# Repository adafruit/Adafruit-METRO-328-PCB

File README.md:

## Adafruit METRO 328 PCB

<a href="http://www.adafruit.com/products/2466"><br/>
Click here to purchase one from the Adafruit shop</a>

PCB files for the Adafruit METRO 328. Format is EagleCAD schematic and board layout

For more details, check out the product page at
* https://www.adafruit.com/products/2466

### Description

We sure love the ATmega328 here at Adafruit, and we use them a lot for our own projects. The processor has plenty of GPIO, Analog inputs, hardware UART SPI and I2C, timers and PWM galore - just enough for most simple projects. When we need to go small, we use a Metro Mini, but when size isn't as much of a concern, and a USB-serial converter is required, we reach for an Adafruit METRO.

METRO is the culmination of years of playing with AVRs: we wanted to make a development board that is easy to use and is hacker friendly.

ATmega328 brains - This popular chip has 32KB of flash (1/2 K is reserved for the bootloader), 2KB of RAM, clocked at 16MHz
Power the METRO with 7-9V polarity protected DC or the micro USB connector to any 5V USB source. The 2.1mm DC jack has an on/off switch next to it so you can turn off your setup easily. The METRO will automagically switch between USB and DC.
METRO has 20 GPIO pins, 6 of which are Analog in as well, and 2 of which are reserved for the USB-serial converter. There's also 6 PWMs available on 3 timers (1 x 16-bit, 2 x 8-bit). There's a hardware SPI port, hardware I2C port and hardware UART to USB.
GPIO Logic level is 5V but by cutting and soldering closed a jumper, you can easily convert it to 3.3V logic
USB to Serial converter, there's a hardware USB to Serial converter that can be used by any computer to listen/send data to the METRO, and can also be used to launch and update code via the bootloader
Four indicator LEDs, on the front edge of the PCB, for easy debugging. One green power LED, two RX/TX LEDs for the UART, and a red LED connected to pin PB5
Easy reprogramming, comes pre-loaded with the Optiboot bootloader, which is supported by avrdude and only uses 512 bytes.
Beautiful styling by PaintYourDragon and Bruce Yan, in Adafruit Black with gold plated pads.
Works with all Adafruit designed shields!
This version of the METRO 328 comes as a fully assembled and tested development board but without any headers or the DC jack attached. We do include these parts so that you can solder on if you like, or you can solder wires or header directly to the breakout pads. We also include 4 rubber bumpers to keep it from slipping off your desk.

### License

Adafruit invests time and resources providing this open source design, please support Adafruit and open-source hardware by purchasing products from [Adafruit](https://www.adafruit.com)!

Designed by Limor Fried/Ladyada for Adafruit Industries.

Creative Commons Attribution/Share-Alike. See license.txt for additional details.

Derivative of "Arduino UNO R3 Reference design" (http://www.arduino.cc/en/Main/ArduinoBoardUno)

All text above must be included in any redistribution

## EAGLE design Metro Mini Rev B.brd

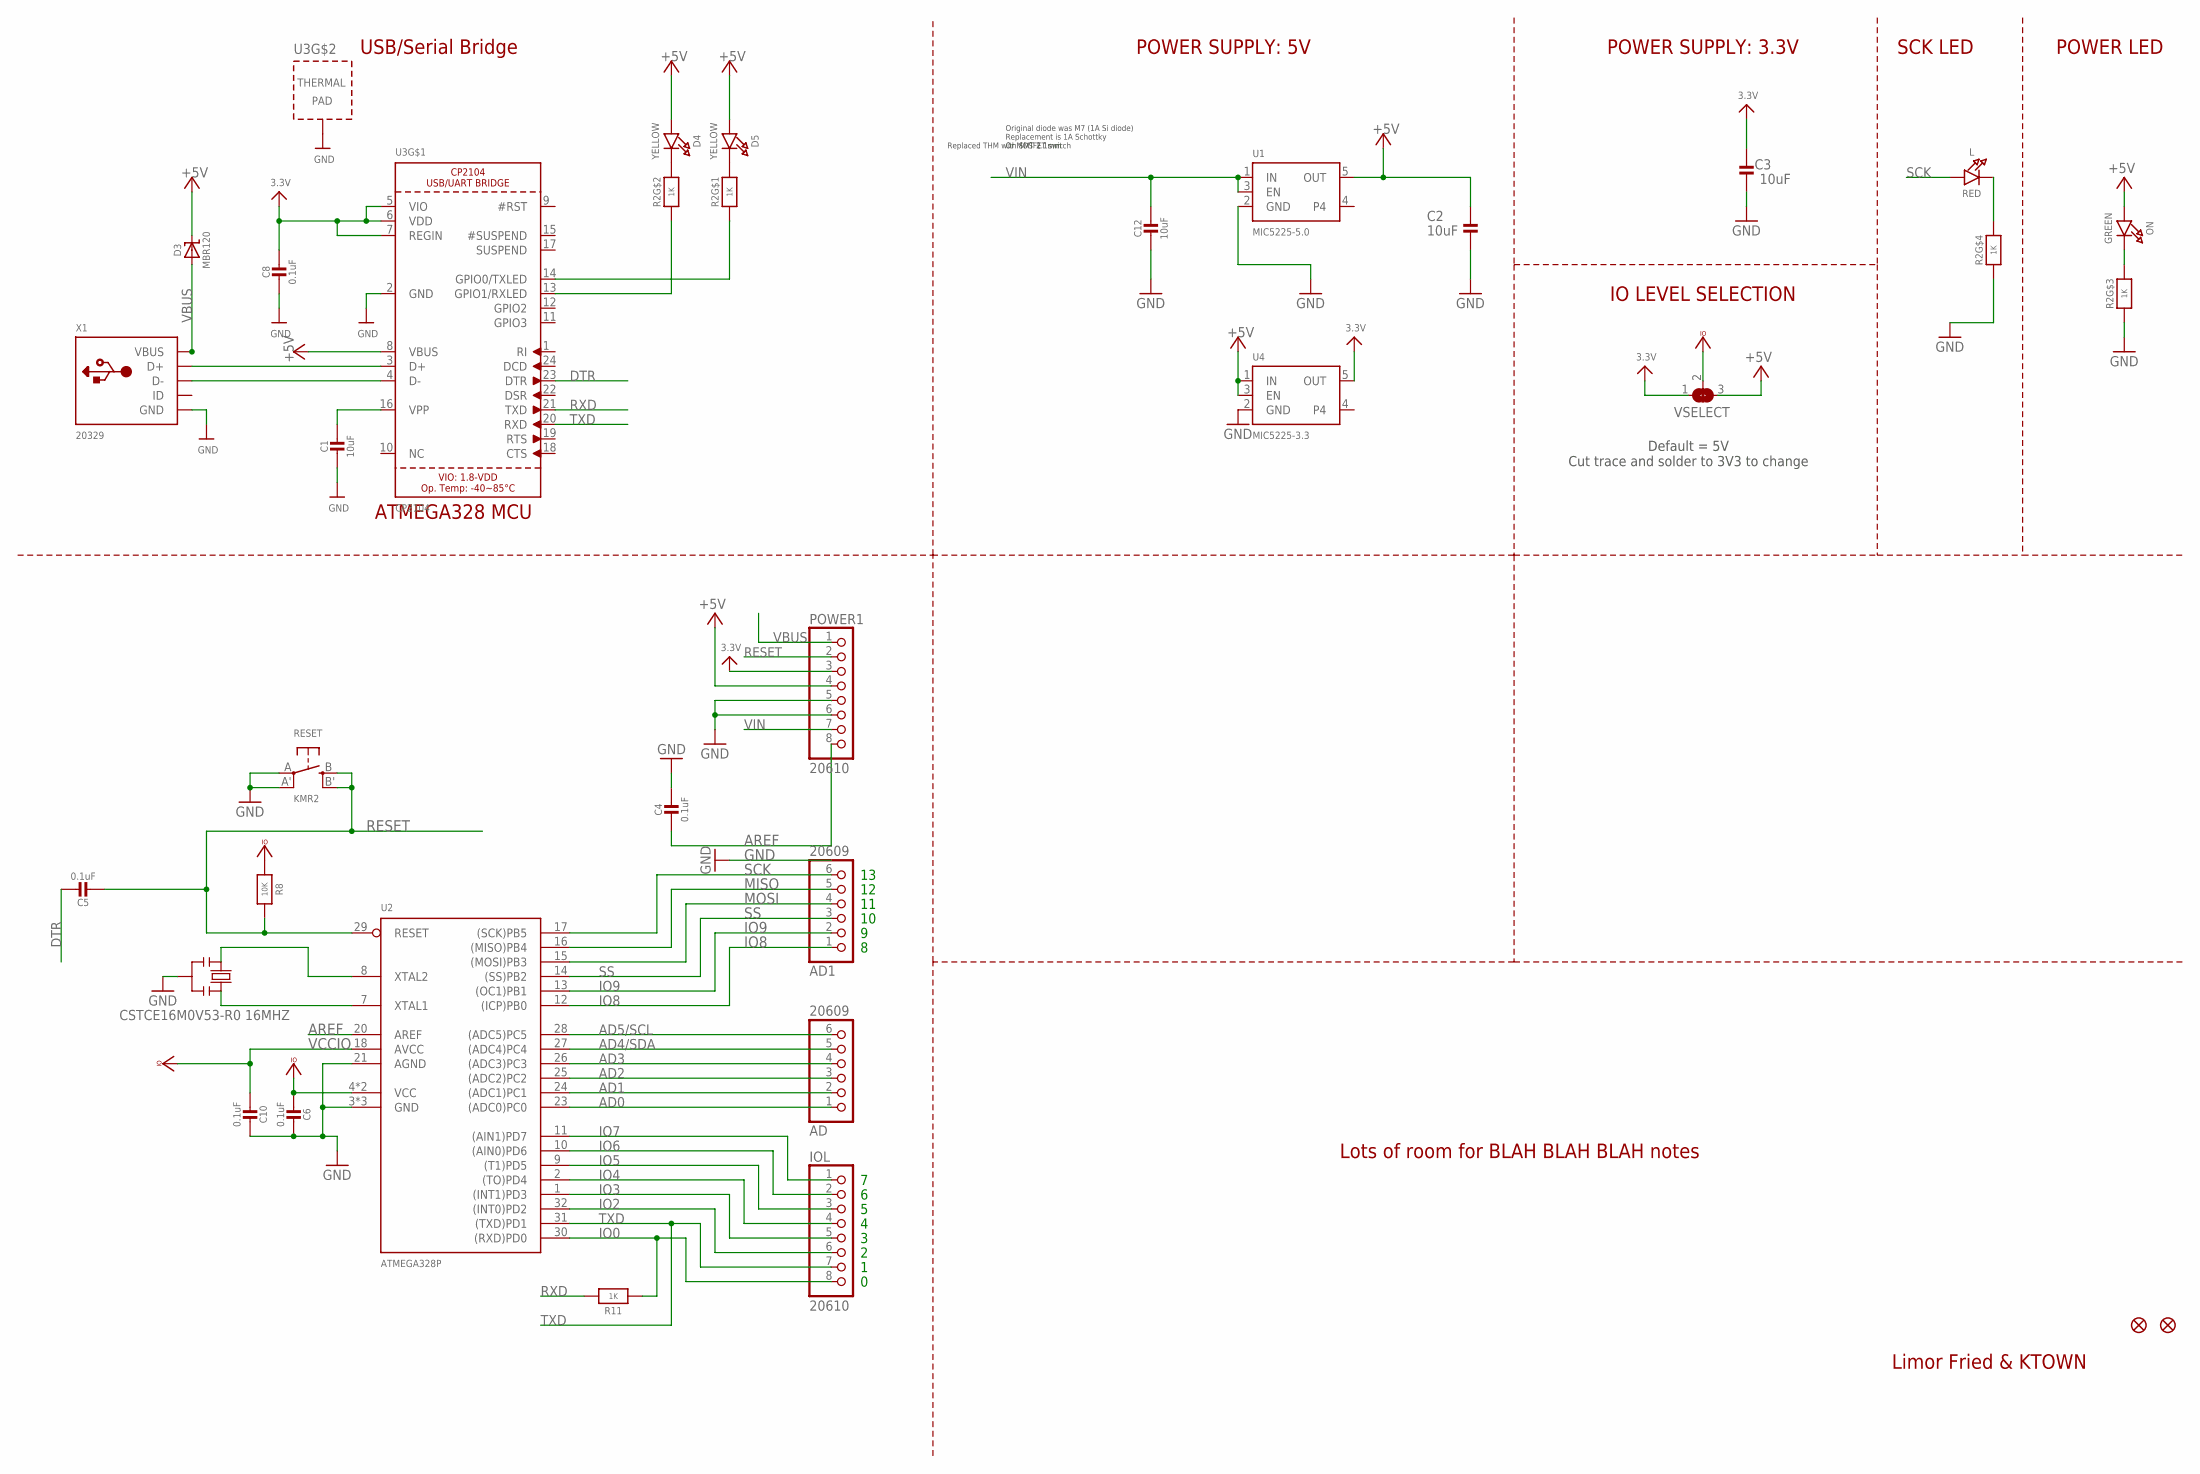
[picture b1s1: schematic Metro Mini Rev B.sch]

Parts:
AD, AD1: 20609; 1X06_ROUND
C1, C2, C3, C12: 10uF; 0805-NO
C4, C6, C8, C10: 0.1uF; 0805-NO
C5: 0.1uF; _0805MP
D3: MBR120; SOD-123
D4, D5: YELLOW; CHIPLED_0805_NOOUTLINE
FD1, FD2: FIDUCIAL""; FIDUCIAL_1MM
IOL: 20610; 1X08_ROUND
L: RED; CHIPLED_0805_NOOUTLINE
ON: GREEN; CHIPLED_0805_NOOUTLINE
POWER1: 20610; 1X08_ROUND_70
R2: 1K; RESPACK_4X0603
R8: 10K; 0805-NO
R11: 1K; 0805-NO
RESET: KMR2; BTN_KMR2_4.6X2.8
U1: MIC5225-5.0; SOT23-5
U2: ATMEGA328P; MLF32-TH
U3: CP2104; QFN24_4MM_SMSC
U4: MIC5225-3.3; SOT23-5
VSELECT: SOLDERJUMPER_2WAY; SOLDERJUMPER_2WAY_OPEN_NOPASTE
X1: 20329; 4UCONN_20329_V2
Y2: CSTCE16M0V53-R0 16MHZ; RESONATOR

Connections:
3.3V: C3.2, C8.1, POWER1.3, U3.5 (VIO), U3.6 (VDD), U3.7 (REGIN), U4.5 (OUT), VSELECT.1
+5V: C2.2, D3.C, D4.A, D5.A, ON.A, POWER1.4, U1.5 (OUT), U3.8 (VBUS), U4.1 (IN), U4.3 (EN), VSELECT.3
AD0: AD.1, U2.23 ((ADC0)PC0)
AD1: AD.2, U2.24 ((ADC1)PC1)
AD2: AD.3, U2.25 ((ADC2)PC2)
AD3: AD.4, U2.26 ((ADC3)PC3)
AD4/SDA: AD.5, U2.27 ((ADC4)PC4)
AD5/SCL: AD.6, U2.28 ((ADC5)PC5)
AREF: C4.2, POWER1.8, U2.20 (AREF)
DTR: C5.1, U3.23 (DTR)
GND: C1.2, C2.1, C3.1, C4.1, C6.1, C8.2, C10.1, C12.2, POWER1.5, POWER1.6, R2.3 (1), R2.4 (1), RESET.A, RESET.A' (P1), U1.2 (GND), U2.3 (GND), U2.5 (GND), U2.21 (AGND), U2.TH (GND), U3.2 (GND), U3.THERM (TP), U4.2 (GND), X1.BASE@1 (GND), X1.BASE@2 (GND), X1.GND, X1.SPRT@1 (GND), X1.SPRT@2 (GND), X1.SPRT@3 (GND), X1.SPRT@4 (GND), Y2.2
IO0: IOL.8, R11.1, U2.30 ((RXD)PD0)
IO2: IOL.6, U2.32 ((INT0)PD2)
IO3: IOL.5, U2.1 ((INT1)PD3)
IO4: IOL.4, U2.2 ((TO)PD4)
IO5: IOL.3, U2.9 ((T1)PD5)
IO6: IOL.2, U2.10 ((AIN0)PD6)
IO7: IOL.1, U2.11 ((AIN1)PD7)
IO8: AD1.1, U2.12 ((ICP)PB0)
IO9: AD1.2, U2.13 ((OC1)PB1)
MISO: AD1.5, U2.16 ((MISO)PB4)
MOSI: AD1.4, U2.15 ((MOSI)PB3)
unnamed: L.C, R2.5 (2)
unnamed: ON.C, R2.6 (2)
unnamed: R2.1, U3.14 (GPIO0/TXLED)
unnamed: D4.C, R2.7 (2)
unnamed: D5.C, R2.8 (2)
unnamed: U3.3 (D+), X1.D+
unnamed: U3.4 (D-), X1.D-
unnamed: C1.1, U3.16 (VPP)
unnamed: R2.2 (1), U3.13 (GPIO1/RXLED)
RESET: C5.2, POWER1.2, R8.1, RESET.B (S), RESET.B' (S1), U2.29 (RESET)
RXD: R11.2, U3.21 (TXD)
SCK: AD1.6, L.A, U2.17 ((SCK)PB5)
SS: AD1.3, U2.14 ((SS)PB2)
TXD: IOL.7, U2.31 ((TXD)PD1), U3.20 (RXD)
VBUS: D3.A, POWER1.1, X1.VBUS
VCCIO: C6.2, C10.2, R8.2, U2.4 (VCC), U2.6 (VCC), U2.18 (AVCC), VSELECT.2
VIN: C12.1, POWER1.7, U1.1 (IN), U1.3 (EN)
XTAL1: U2.7 (XTAL1), Y2.3
XTAL2: U2.8 (XTAL2), Y2.1

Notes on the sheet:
Limor Fried & KTOWN
Original diode was M7 (1A Si diode) Replacement is 1A Schottky Or MOSFET switch
Replaced THM with SMT 2.1mm
POWER SUPPLY: 5V
USB/Serial Bridge
POWER SUPPLY: 3.3V
IO LEVEL SELECTION
POWER LED
ATMEGA328 MCU
SCK LED
Lots of room for BLAH BLAH BLAH notes
Default = 5V Cut trace and solder to 3V3 to change

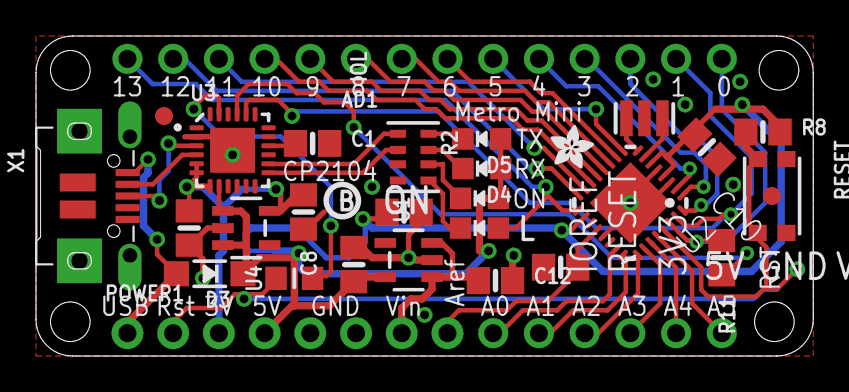
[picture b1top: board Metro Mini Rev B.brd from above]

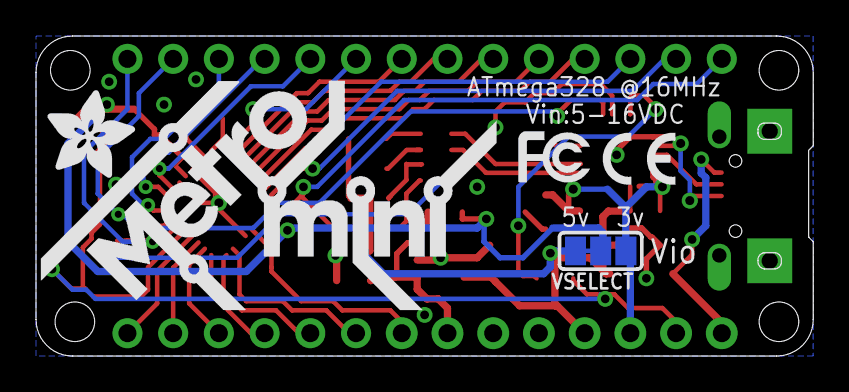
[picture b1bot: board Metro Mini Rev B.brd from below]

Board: 2 copper layers, 43.2 x 17.8 mm, 37 parts (5 on the bottom side), 41 nets.

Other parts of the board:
U$4: PCBFEAT-REV-040
U$5: ADAFRUIT_2.5MM
U$7: METROMINI_SILK
U$10: ADAFRUIT_5MM
U$12: SYMBOL_CE_TINY
U$14: SYMBOL_FCC_TINY

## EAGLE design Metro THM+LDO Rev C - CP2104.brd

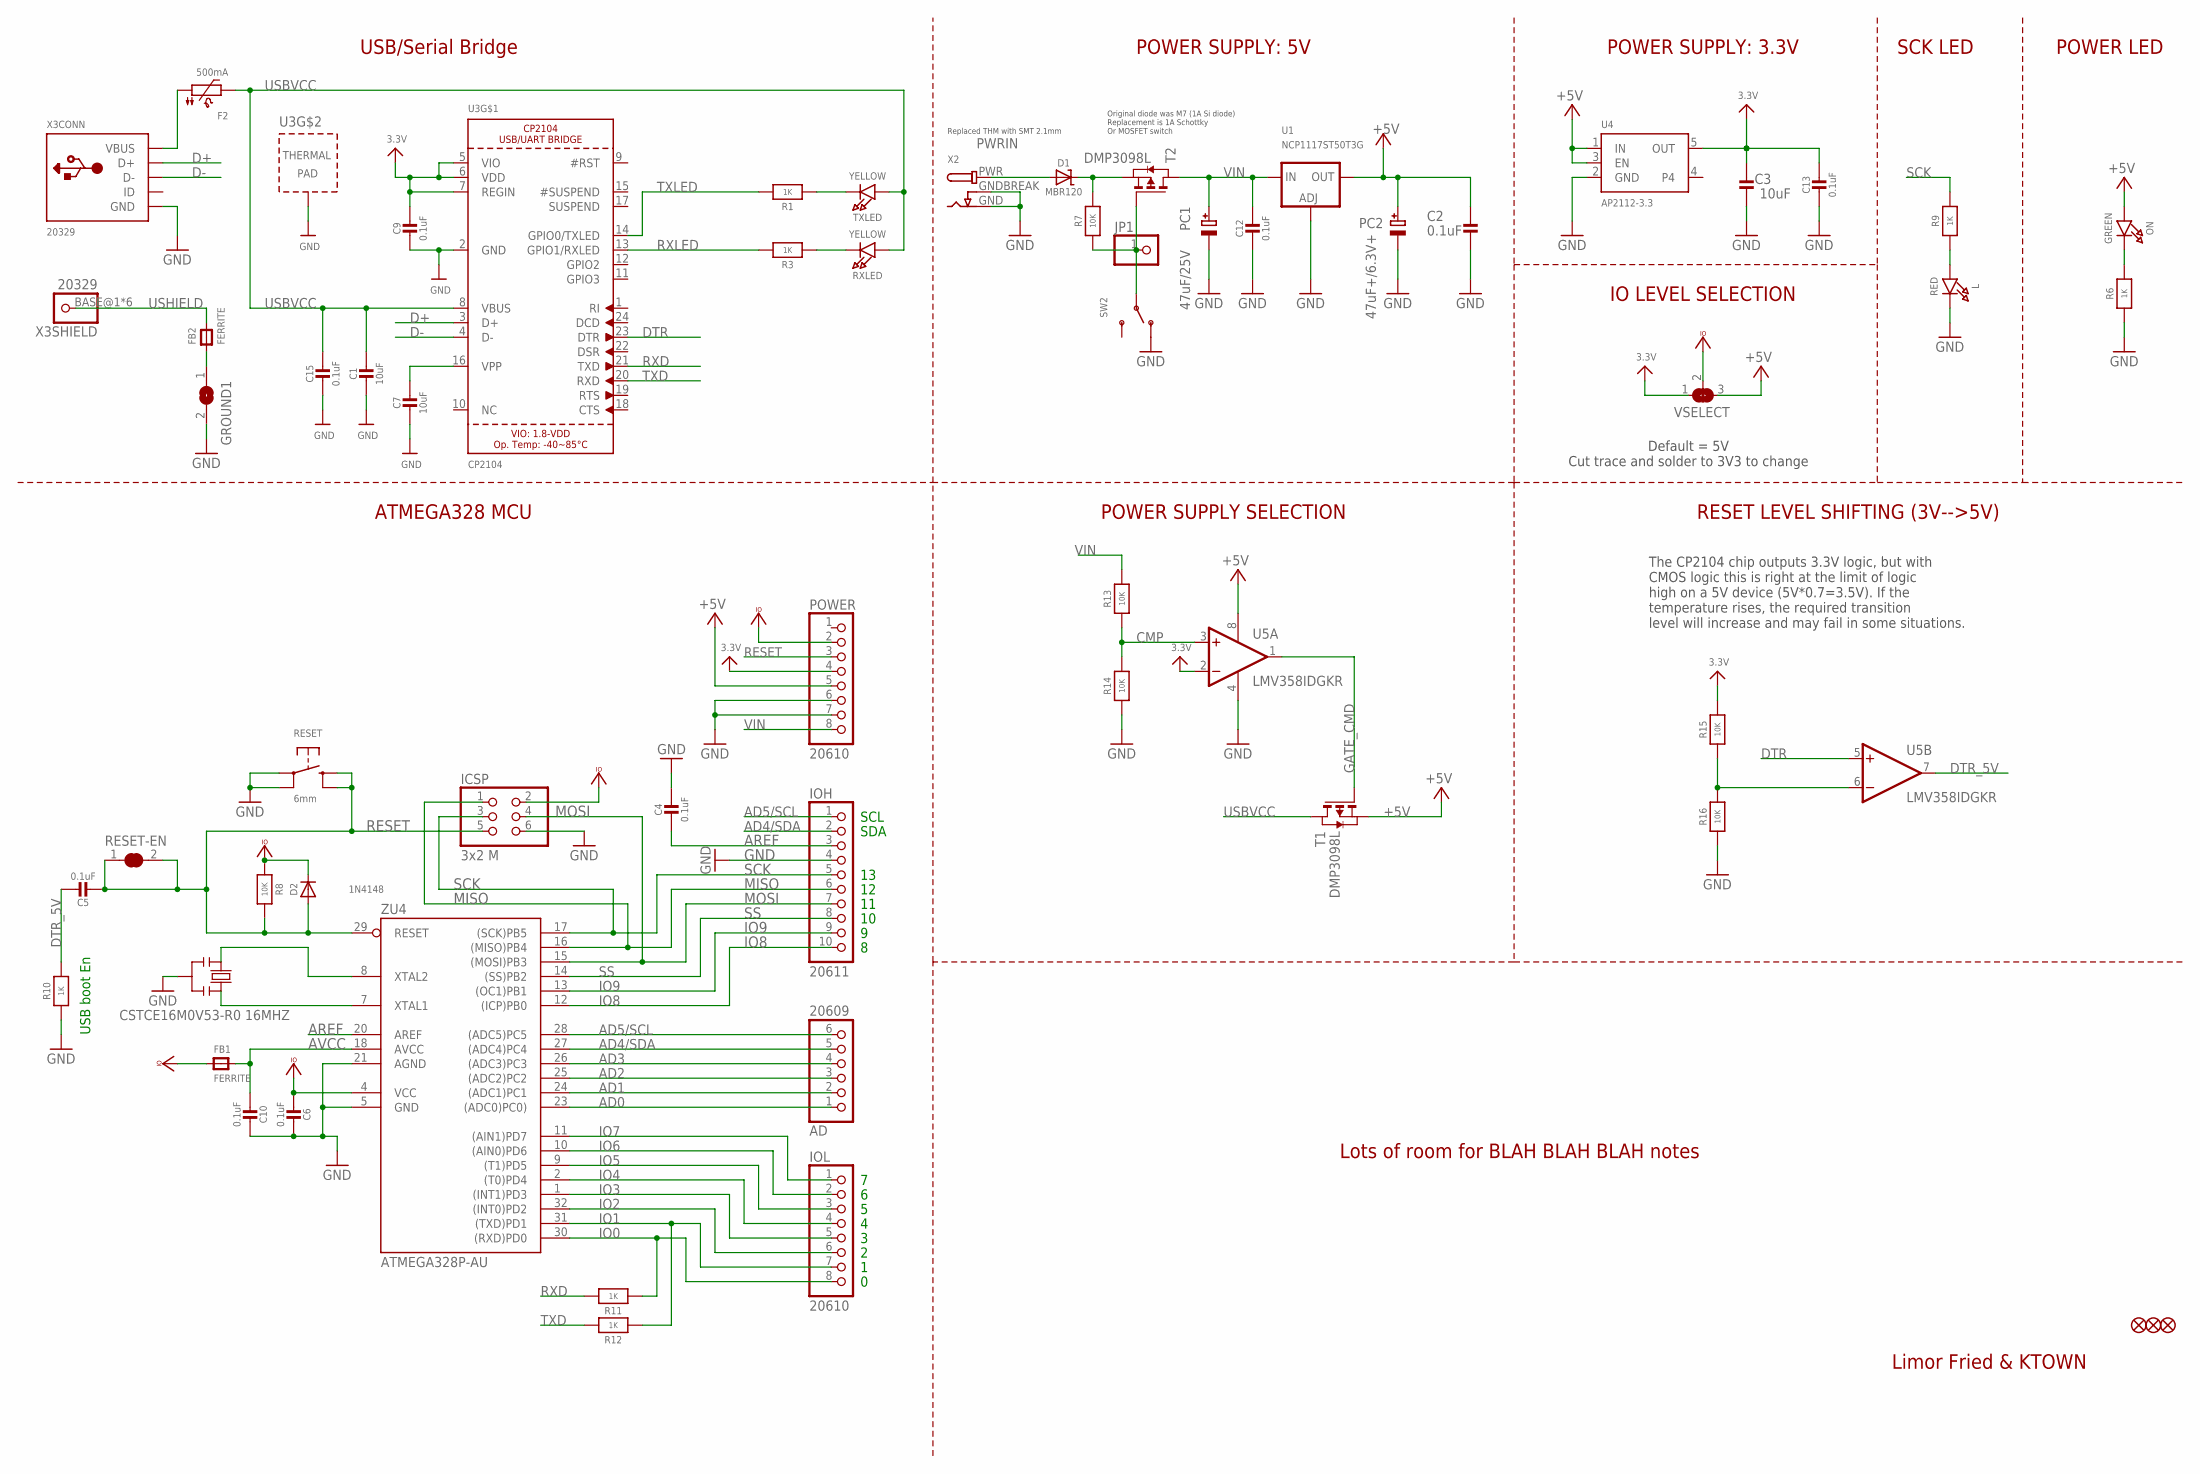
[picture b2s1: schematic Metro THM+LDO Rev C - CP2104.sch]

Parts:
AD: 20609; 1X06_OVAL
C1, C3, C7: 10uF; 0805-NO
C2, C4, C5, C6, C9, C12, C13, C15: 0.1uF; 0805-NO
C10: 0.1uF; 0805_10MGAP
D1: MBR120; SOD-123
D2: 1N4148; SOD-323
F2: 500mA; 1206-NO
FB1, FB2: FERRITE; 0805-NO
FD1, FD2, FD3: FIDUCIAL_1MM
GROUND1: SJ
ICSP: 3x2 M; 2X03_ROUND_70MIL
IOH: 20611; 1X10_OVAL
IOL: 20610; 1X08_OVAL
JP1: HEADER-1X1ROUND; 1X01_ROUND
L: RED; CHIPLED_0805_NOOUTLINE
ON: GREEN; CHIPLED_0805_NOOUTLINE
PC1: 47uF/25V; PANASONIC_D
PC2: 47uF+/6.3V+; PANASONIC_D
POWER: 20610; 1X08_OVAL
R1, R3, R6, R9, R10, R11, R12: 1K; 0805-NO
R7, R13, R14, R15, R16: 10K; 0805-NO
R8: 10K; _0805MP
RESET: 6mm; EVQ-Q2
RESET-EN: SOLDERJUMPER_CLOSED; SOLDERJUMPER_CLOSEDWIRE
RXLED: YELLOW; CHIPLED_0805_NOOUTLINE
SW2: SWITCH_SPDT; SPDT_SMT_SSSS811101
T1, T2: DMP3098L; SOT-23
TXLED: YELLOW; CHIPLED_0805_NOOUTLINE
U1: NCP1117ST50T3G; SOT223-R
U3: CP2104; QFN24_4MM_SMSC
U4: AP2112-3.3; SOT23-5
U5: LMV358IDGKR; MSOP08
VSELECT: SOLDERJUMPER_2WAY; SOLDERJUMPER_2WAY_OPEN_NOPASTE
X2: DCBARRELPTH; DCJACK_2MM_PTH
X3: 20329; 4UCONN_20329_V2
Y2: CSTCE16M0V53-R0 16MHZ; RESONATOR
ZU4: ATMEGA328P-AU; TQFP32-08

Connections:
3.3V: C3.2, C9.1, C13.1, POWER.4, R15.2, U3.5 (VIO), U3.6 (VDD), U3.7 (REGIN), U4.5 (OUT), U5.2 (-IN), VSELECT.1
+5V: C2.2, ON.A, PC2.+, POWER.5, T1.2 (S), U1.2 (OUT), U1.4 (OUT), U4.1 (IN), U4.3 (EN), U5.8 (V+), VSELECT.3
AD0: AD.1, ZU4.23 ((ADC0)PC0))
AD1: AD.2, ZU4.24 ((ADC1)PC1)
AD2: AD.3, ZU4.25 ((ADC2)PC2)
AD3: AD.4, ZU4.26 ((ADC3)PC3)
AD4/SDA: AD.5, IOH.2, ZU4.27 ((ADC4)PC4)
AD5/SCL: AD.6, IOH.1, ZU4.28 ((ADC5)PC5)
AREF: C4.2, IOH.3, ZU4.20 (AREF)
AVCC: C10.2, FB1.2, ZU4.18 (AVCC)
CMP: R13.1, R14.2, U5.3 (+IN)
D+: U3.3 (D+), X3.D+
D-: U3.4 (D-), X3.D-
DTR: U3.23 (DTR), U5.5 (+IN)
DTR_5V: C5.1, R10.2, U5.7 (OUT)
GATE_CMD: T1.3 (G), U5.1 (OUT)
GND: C1.2, C2.1, C3.1, C4.1, C6.1, C7.2, C9.2, C10.1, C12.2, C13.2, C15.2, GROUND1.2, ICSP.6, IOH.4, L.C, PC1.-, PC2.-, POWER.6, POWER.7, R6.1, R10.1, R14.1, R16.1, RESET.A, RESET.A' (P1), SW2.A (O), U1.1 (ADJ), U3.2 (GND), U3.THERM (TP), U4.2 (GND), U5.4 (V-), X2.GND, X2.GNDBREAK, X3.GND, Y2.2, ZU4.5 (GND), ZU4.21 (AGND)
IO0: IOL.8, R11.1, ZU4.30 ((RXD)PD0)
IO1: IOL.7, R12.1, ZU4.31 ((TXD)PD1)
IO2: IOL.6, ZU4.32 ((INT0)PD2)
IO3: IOL.5, ZU4.1 ((INT1)PD3)
IO4: IOL.4, ZU4.2 ((T0)PD4)
IO5: IOL.3, ZU4.9 ((T1)PD5)
IO6: IOL.2, ZU4.10 ((AIN0)PD6)
IO7: IOL.1, ZU4.11 ((AIN1)PD7)
IO8: IOH.10, ZU4.12 ((ICP)PB0)
IO9: IOH.9, ZU4.13 ((OC1)PB1)
MISO: ICSP.1, IOH.6, ZU4.16 ((MISO)PB4)
MOSI: ICSP.4, IOH.7, ZU4.15 ((MOSI)PB3)
unnamed: L.A, R9.1
unnamed: FB2.1, GROUND1.1
unnamed: ON.C, R6.2
unnamed: R3.1, RXLED.C
unnamed: R1.1, TXLED.C
unnamed: R15.1, R16.2, U5.6 (-IN)
unnamed: JP1.1, R7.1, SW2.B, T2.3 (G)
unnamed: D1.C, R7.2, T2.2 (S)
unnamed: C7.1, U3.16 (VPP)
PWRIN: D1.A, X2.PWR
RESET: C5.2, D2.A, ICSP.5, POWER.3, R8.1, RESET.B (S), RESET.B' (S1), RESET-EN.1, RESET-EN.2, ZU4.29 (RESET)
RXD: R11.2, U3.21 (TXD)
RXLED: R3.2, U3.13 (GPIO1/RXLED)
SCK: ICSP.3, IOH.5, R9.2, ZU4.17 ((SCK)PB5)
SS: IOH.8, ZU4.14 ((SS)PB2)
TXD: R12.2, U3.20 (RXD)
TXLED: R1.2, U3.14 (GPIO0/TXLED)
USBVCC: C1.1, C15.1, F2.2, RXLED.A, T1.1 (D), TXLED.A, U3.8 (VBUS)
USHIELD: FB2.2, X3.BASE@1 (1), X3.BASE@2 (1), X3.SPRT@1 (1), X3.SPRT@2 (1), X3.SPRT@3 (1), X3.SPRT@4 (1)
VBUS: F2.1, X3.VBUS
VCCIO: C6.2, D2.C, FB1.1, ICSP.2, POWER.2, R8.2, VSELECT.2, ZU4.4 (VCC)
VIN: C12.1, PC1.+, POWER.8, R13.2, T2.1 (D), U1.3 (IN)
XTAL1: Y2.3, ZU4.7 (XTAL1)
XTAL2: Y2.1, ZU4.8 (XTAL2)

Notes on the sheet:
USB boot En
SDA
SCL
Limor Fried & KTOWN
Original diode was M7 (1A Si diode) Replacement is 1A Schottky Or MOSFET switch
Replaced THM with SMT 2.1mm
POWER SUPPLY: 5V
USB/Serial Bridge
POWER SUPPLY: 3.3V
IO LEVEL SELECTION
POWER LED
ATMEGA328 MCU
POWER SUPPLY SELECTION
SCK LED
Lots of room for BLAH BLAH BLAH notes
Default = 5V Cut trace and solder to 3V3 to change
RESET LEVEL SHIFTING (3V-->5V)
The CP2104 chip outputs 3.3V logic, but with CMOS logic this is right at the limit of logic high on a 5V device (5V*0.7=3.5V). If the temperature rises, the required transition level will increase and may fail in some situations.

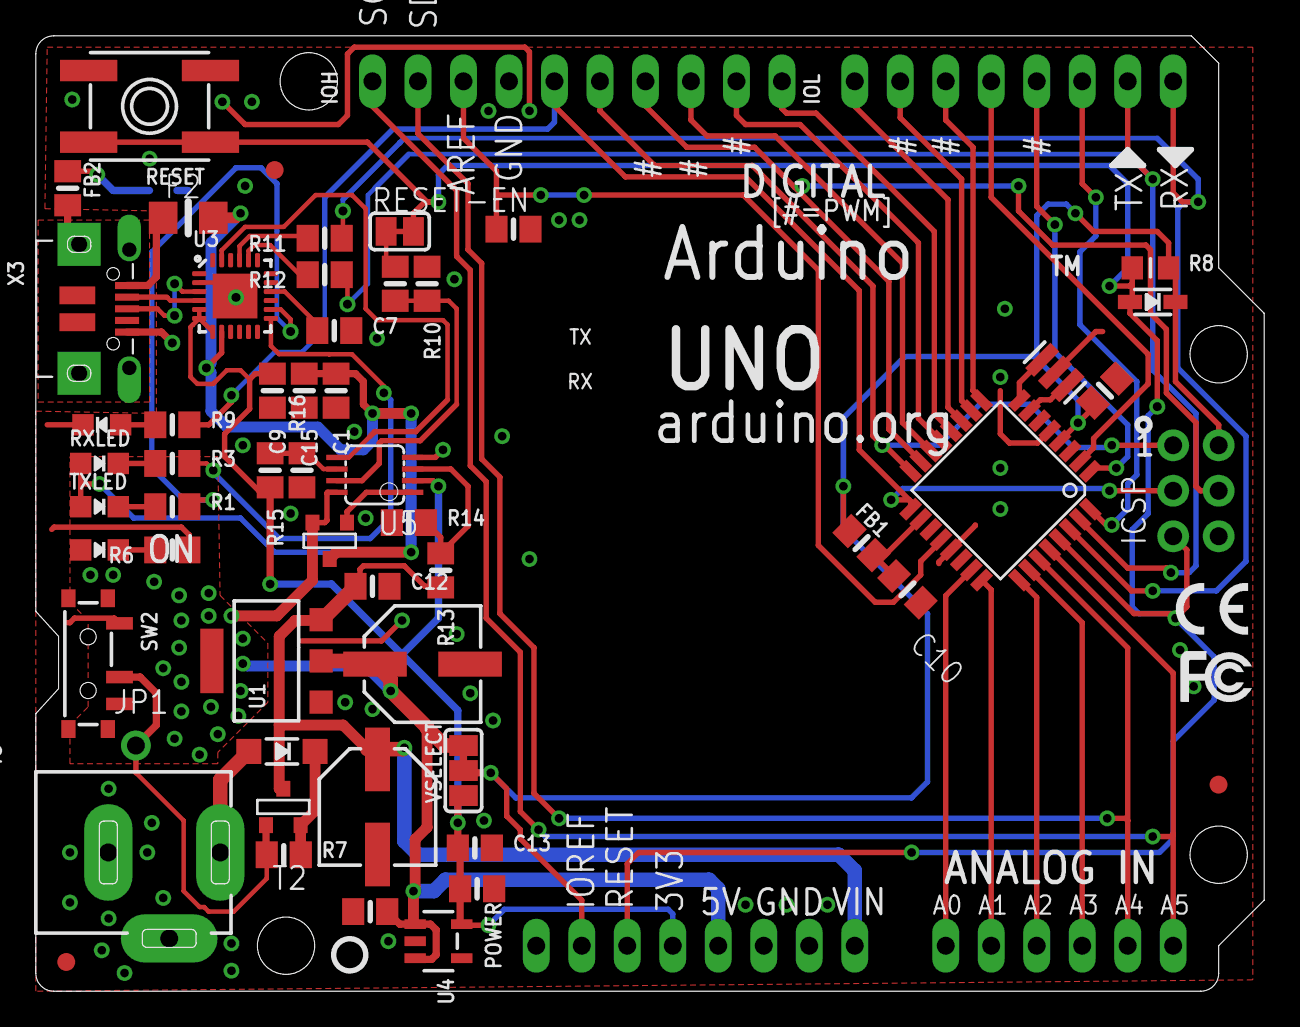
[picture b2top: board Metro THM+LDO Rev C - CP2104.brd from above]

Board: 2 copper layers, 68.6 x 53.3 mm, 65 parts (1 on the bottom side), 53 nets.

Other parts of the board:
U$4: METROSILK_CP2104_TOP
U$14: METROSILK_BOT
U$15: PCBFEAT-REV-040
U$16: SYMBOL_FCC_TINY
U$17: SYMBOL_CE_TINY

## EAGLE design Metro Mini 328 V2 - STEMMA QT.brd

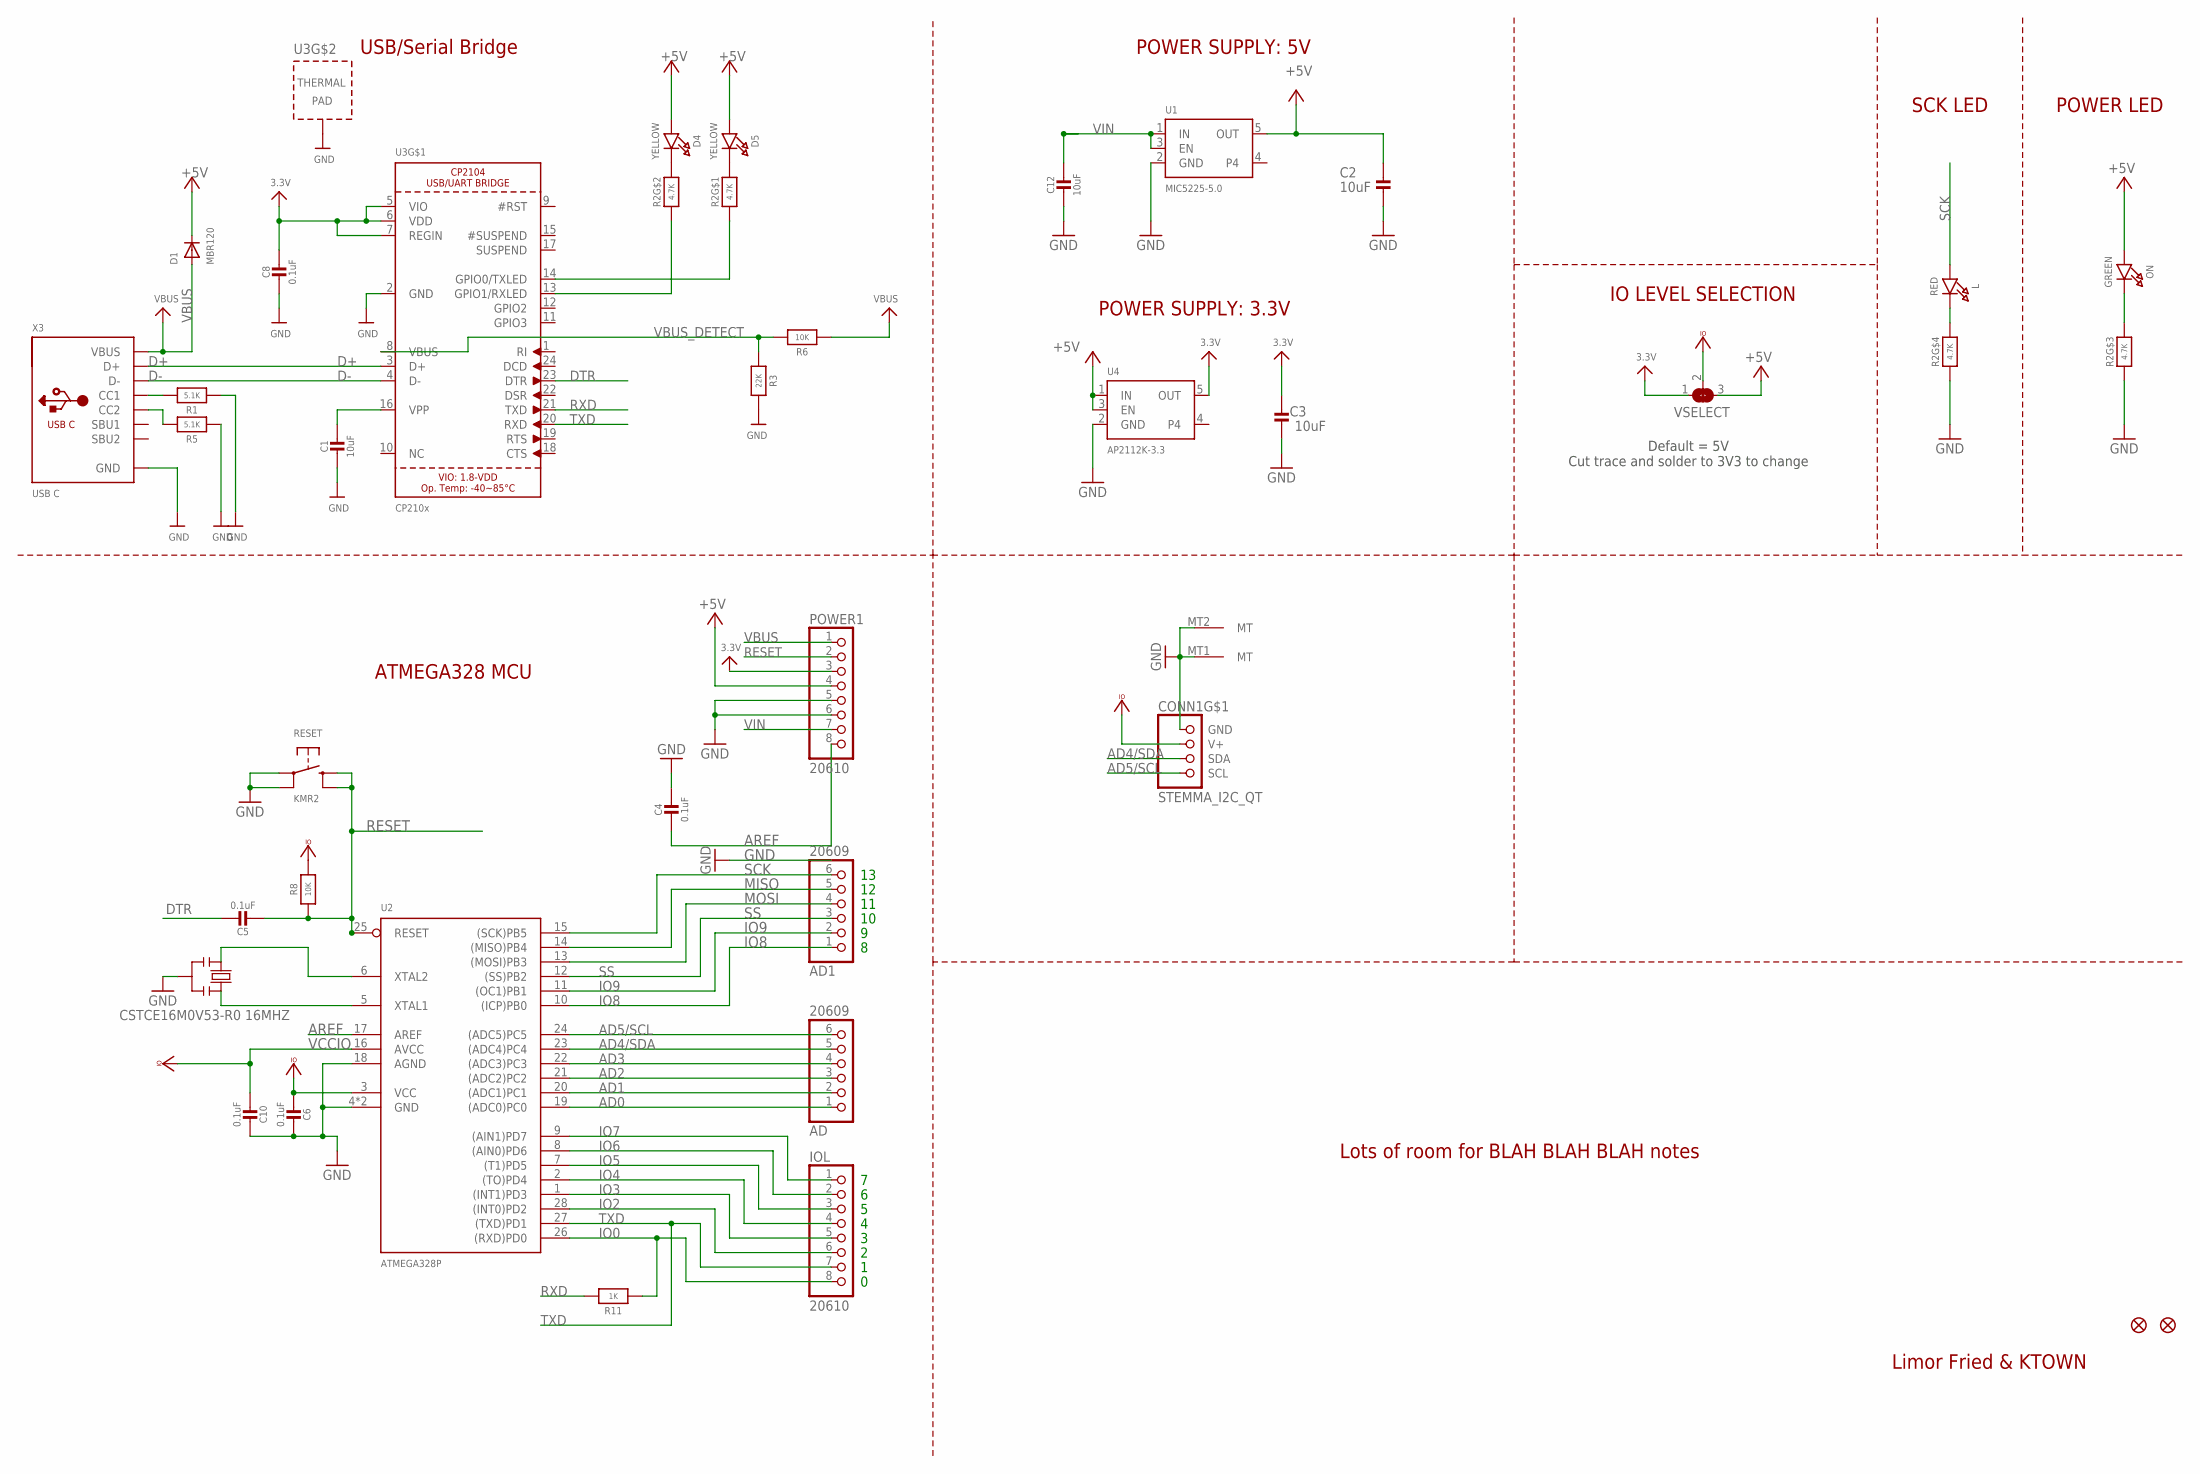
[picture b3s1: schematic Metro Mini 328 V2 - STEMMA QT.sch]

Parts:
AD, AD1: 20609; 1X06_ROUND
C1, C2, C3, C12: 10uF; 0805-NO
C4, C5, C6, C8, C10: 0.1uF; 0603-NO
CONN1: STEMMA_I2C_QT; JST_SH4
D1: MBR120; SOD-123FL
D4, D5: YELLOW; CHIPLED_0603_NOOUTLINE
FD1, FD2: FIDUCIAL_1MM
IOL: 20610; 1X08_ROUND
L: RED; CHIPLED_0603_NOOUTLINE
ON: GREEN; CHIPLED_0603_NOOUTLINE
POWER1: 20610; 1X08_ROUND_70
R1, R5: 5.1K; 0603-NO
R2: 4.7K; RESPACK_4X0603
R3: 22K; 0603-NO
R6, R8: 10K; 0603-NO
R11: 1K; 0603-NO
RESET: KMR2; BTN_KMR2_4.6X2.8
U1: MIC5225-5.0; SOT23-5
U2: ATMEGA328P; QFN28_4MM_.45MM
U3: CP210x; QFN24_4MM_SMSC
U4: AP2112K-3.3; SOT23-5
VSELECT: SOLDERJUMPER_2WAY; SOLDERJUMPER_2WAY_OPEN_NOPASTE
X3: USB C; USB_C_CUSB31-CFM2AX-01-X
Y2: CSTCE16M0V53-R0 16MHZ; RESONATOR

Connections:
3.3V: C3.2, C8.1, POWER1.3, U3.5 (VIO), U3.6 (VDD), U3.7 (REGIN), U4.5 (OUT), VSELECT.1
+5V: C2.2, D1.C, D4.A, D5.A, ON.A, POWER1.4, U1.5 (OUT), U4.1 (IN), U4.3 (EN), VSELECT.3
AD0: AD.1, U2.19 ((ADC0)PC0)
AD1: AD.2, U2.20 ((ADC1)PC1)
AD2: AD.3, U2.21 ((ADC2)PC2)
AD3: AD.4, U2.22 ((ADC3)PC3)
AD4/SDA: AD.5, CONN1.3 (SDA), U2.23 ((ADC4)PC4)
AD5/SCL: AD.6, CONN1.4 (SCL), U2.24 ((ADC5)PC5)
AREF: C4.2, POWER1.8, U2.17 (AREF)
D+: U3.3 (D+), X3.A6 (D+), X3.B6 (D+)
D-: U3.4 (D-), X3.A7 (D-), X3.B7 (D-)
DTR: C5.1, U3.23 (DTR)
GND: C1.2, C2.1, C3.1, C4.1, C6.1, C8.2, C10.1, C12.2, CONN1.1 (GND), CONN1.MT1 (MT), CONN1.MT2 (MT), POWER1.5, POWER1.6, R1.1, R2.3 (1), R2.4 (1), R3.1, R5.1, RESET.A, RESET.A' (P1), U1.2 (GND), U2.4 (GND), U2.18 (AGND), U2.29 (GND), U3.2 (GND), U3.THERM (TP), U4.2 (GND), X3.A1B12 (GND), X3.B1A12 (GND), Y2.2
IO0: IOL.8, R11.1, U2.26 ((RXD)PD0)
IO2: IOL.6, U2.28 ((INT0)PD2)
IO3: IOL.5, U2.1 ((INT1)PD3)
IO4: IOL.4, U2.2 ((TO)PD4)
IO5: IOL.3, U2.7 ((T1)PD5)
IO6: IOL.2, U2.8 ((AIN0)PD6)
IO7: IOL.1, U2.9 ((AIN1)PD7)
IO8: AD1.1, U2.10 ((ICP)PB0)
IO9: AD1.2, U2.11 ((OC1)PB1)
MISO: AD1.5, U2.14 ((MISO)PB4)
MOSI: AD1.4, U2.13 ((MOSI)PB3)
unnamed: L.C, R2.5 (2)
unnamed: ON.C, R2.6 (2)
unnamed: R2.1, U3.14 (GPIO0/TXLED)
unnamed: R1.2, X3.A5 (CC1)
unnamed: D4.C, R2.7 (2)
unnamed: D5.C, R2.8 (2)
unnamed: R5.2, X3.B5 (CC2)
unnamed: C1.1, U3.16 (VPP)
unnamed: R2.2 (1), U3.13 (GPIO1/RXLED)
RESET: C5.2, POWER1.2, R8.1, RESET.B (S), RESET.B' (S1), U2.25 (RESET)
RXD: R11.2, U3.21 (TXD)
SCK: AD1.6, L.A, U2.15 ((SCK)PB5)
SS: AD1.3, U2.12 ((SS)PB2)
TXD: IOL.7, U2.27 ((TXD)PD1), U3.20 (RXD)
VBUS: D1.A, POWER1.1, R6.2, X3.A4B9 (VBUS), X3.B4A9 (VBUS)
VBUS_DETECT: R3.2, R6.1, U3.8 (VBUS)
VCCIO: C6.2, C10.2, CONN1.2 (V+), R8.2, U2.3 (VCC), U2.16 (AVCC), VSELECT.2
VIN: C12.1, POWER1.7, U1.1 (IN), U1.3 (EN)
XTAL1: U2.5 (XTAL1), Y2.3
XTAL2: U2.6 (XTAL2), Y2.1

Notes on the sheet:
Limor Fried & KTOWN
POWER SUPPLY: 5V
USB/Serial Bridge
POWER SUPPLY: 3.3V
IO LEVEL SELECTION
POWER LED
ATMEGA328 MCU
SCK LED
Lots of room for BLAH BLAH BLAH notes
Default = 5V Cut trace and solder to 3V3 to change

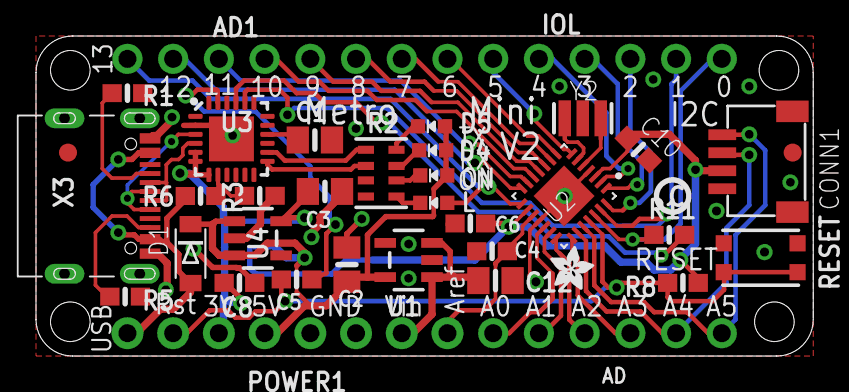
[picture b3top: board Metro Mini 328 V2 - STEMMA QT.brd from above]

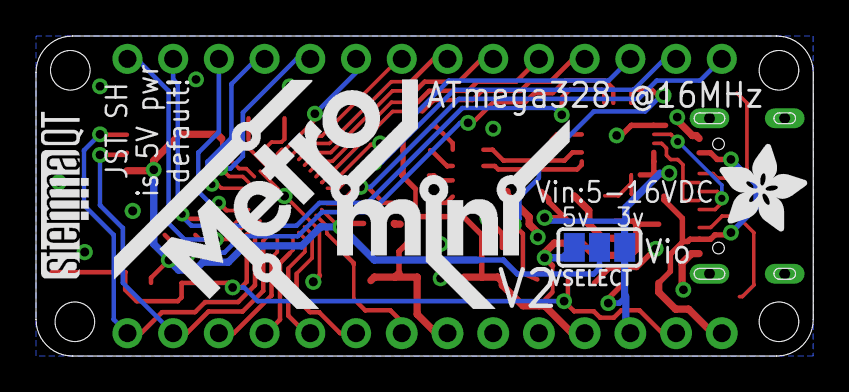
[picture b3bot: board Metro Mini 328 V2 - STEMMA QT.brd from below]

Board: 2 copper layers, 43.2 x 17.8 mm, 41 parts (4 on the bottom side), 44 nets.

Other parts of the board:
U$4: PCBFEAT-REV-040
U$5: ADAFRUIT_2.5MM
U$6: STEMMAQT
U$7: METROMINI_SILK
U$10: ADAFRUIT_5MM

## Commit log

2015-04-28 choo choo here comes METRO!
2015-06-05 mini!
2015-09-27 PDF Board Pin Outs
    Thought I would learn the basics of Eagle Cad and create some pinout
    diagrams for the Metro Boards.
2015-12-08 New Pinout with Schematic
2017-07-26 schem
2017-07-27 https://twitter.com/EMSL/status/890282656532840448
2019-07-16 add cp2104 version
2019-07-16 Readability Improvements to Metro RevC Schematic
    Moved CP2104 from off-page into USB/Serial section of schematic.
    Changed Reset Level Shifting note to correctly refer to the CP2104 instead of the old FTDI chip.
    Moved some things arround slightly to reduce text overlaps.
    Adjusted net routing around CP2104 to improve clarity.
    Added PDF Export for Metro Rev C Schematic.
2021-10-13 Add PrettyPins PDF.
2022-04-05 Updated prettypins
2022-04-06 Added PrettyPins
2022-04-08 Replaced prettypins
2022-08-17 Add Mini V2 board files.

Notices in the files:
parts and their libraries:
microbuilder: This work is placed in the public domain, and may be freely used for commercial and non-commercial work with the following conditions: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
